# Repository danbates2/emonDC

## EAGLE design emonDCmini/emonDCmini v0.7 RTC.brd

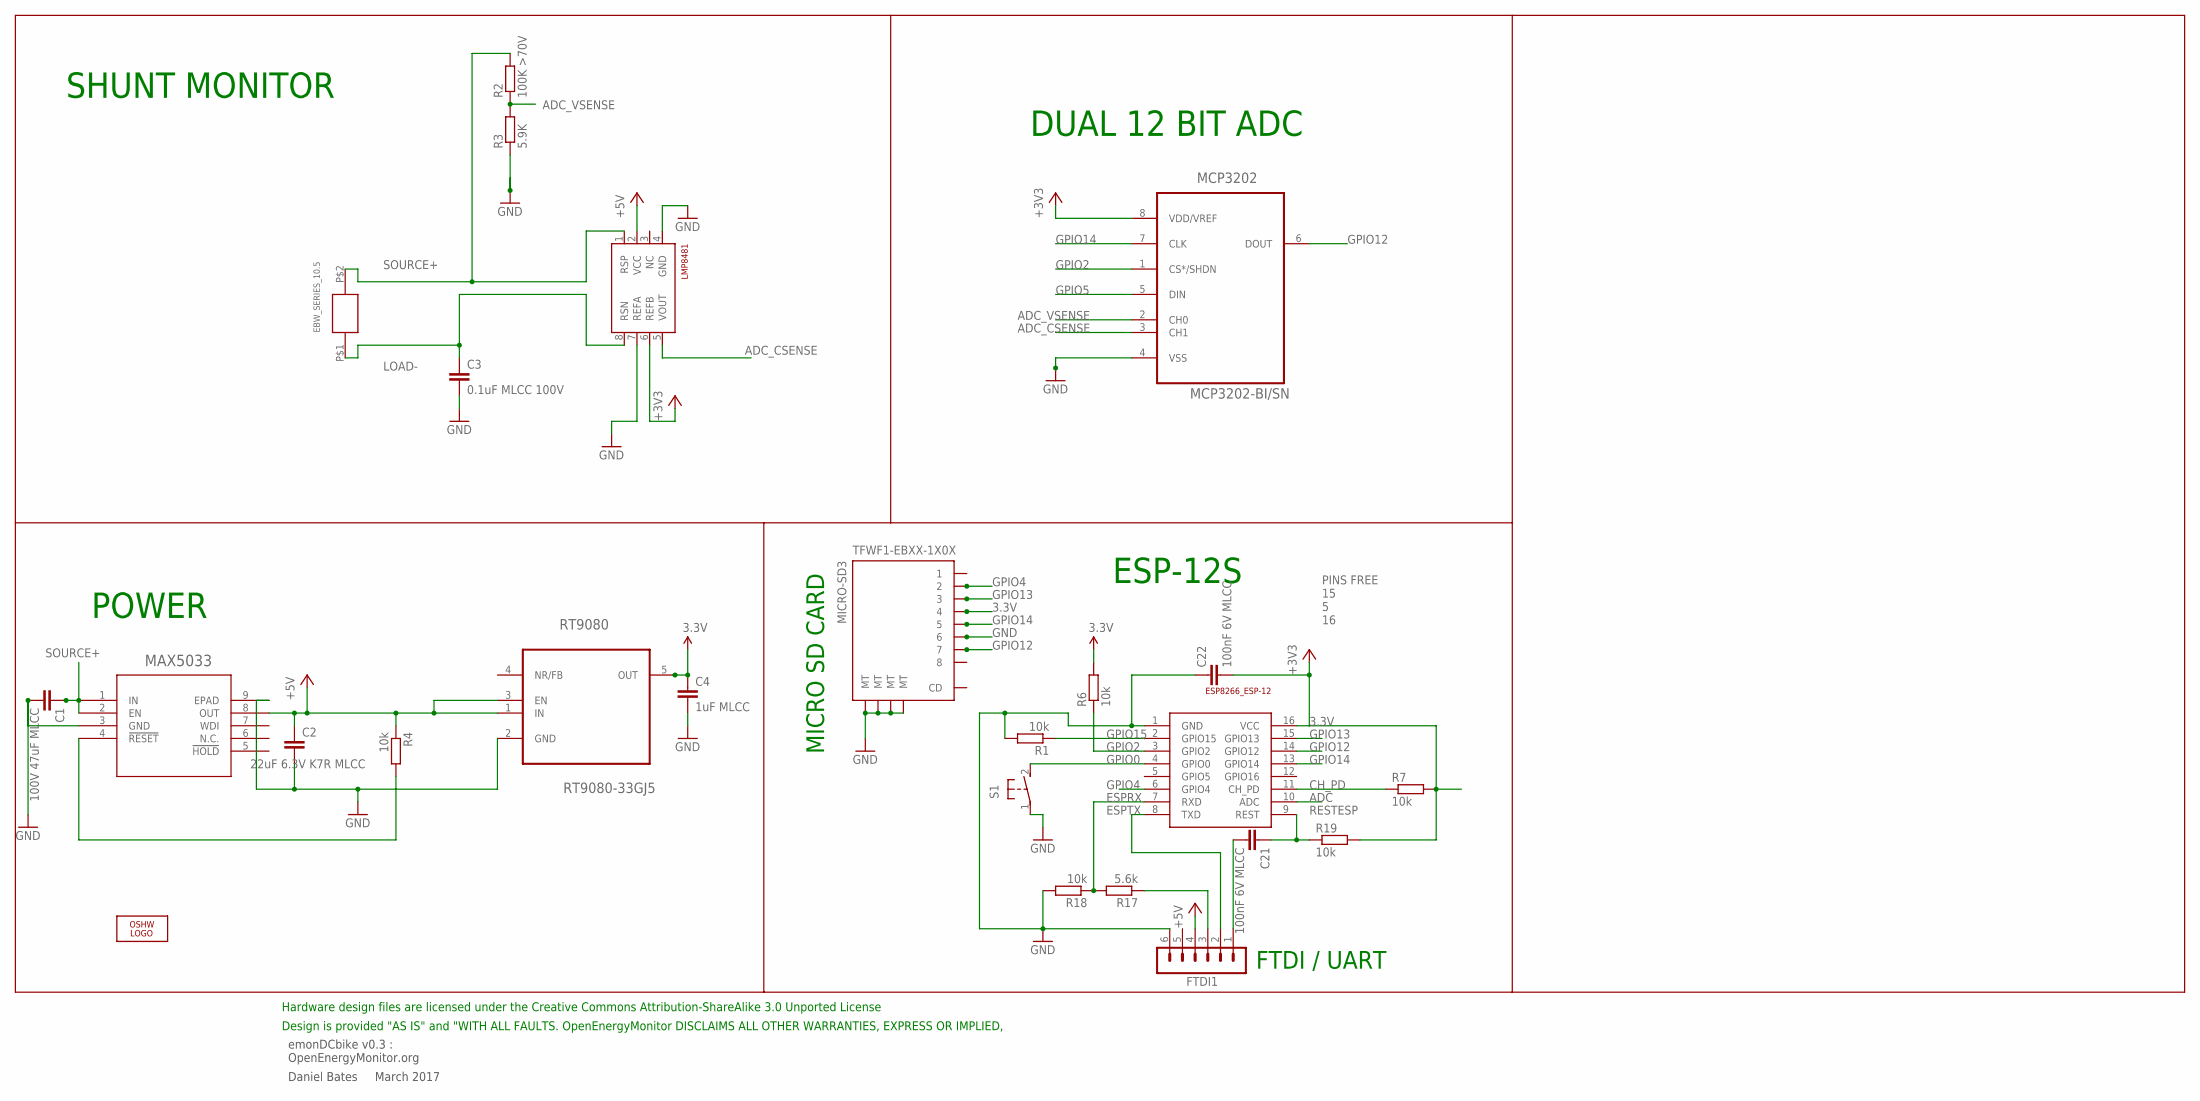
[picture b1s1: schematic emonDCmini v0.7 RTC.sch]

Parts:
C1: 100V 47uF MLCC; C1206
C2: 22uF 6.3V K7R MLCC; C1206
C3: 0.1uF MLCC 100V; C0603
C4: 1uF MLCC; C0603
C21, C22: 100nF 6V MLCC; C0603
EBW_SERIES_10.5: EBW_SERIES_10.5MM
ESP-12: ESP8266_ESP-12; ESP8266-ESP12
FTDI1: FTDI-ESP; MA06-1
LMP8481: LMP8481-H; S-PDSO-G08
LOGO1: OSHW_LOGO_6MILX0200-NT; OSHW_6X200_NOTEXT
MAX5033: MAX5033BUSA+; 21-0111D_SBE-14
MCP3202: MCP3202-BI/SN; SOIC127P600X175-8N
R1, R4, R6, R7, R18, R19: 10k; R0603
R2: 100K >70V; R0603; MPN MCWR06X1003FTL
R3: 5.9K; R0603; MPN MCWR06X5901FTL
R17: 5.6k; R0603
RT9080: RT9080-33GJ5; TSOT-23-5
S1: DTSM-3
TFWF1-EBXX-1X0X: MICRO-SD3; TF-MICRO-SD_PP3*

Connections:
3.3V: C4.1, C22.2, ESP-12.16 (VCC), LMP8481.6 (REFB), MCP3202.8 (VDD/VREF), R6.2, R7.2, R19.2, RT9080.5 (OUT), TFWF1-EBXX-1X0X.4
+5V: C2.1, FTDI1.4, MAX5033.8 (OUT), R4.1, RT9080.1 (IN), RT9080.3 (EN)
ADC: ESP-12.10 (ADC)
ADC_CSENSE: LMP8481.5 (VOUT), MCP3202.3 (CH1)
ADC_VSENSE: MCP3202.2 (CH0), R2.1, R3.2
CH_PD: ESP-12.11 (CH_PD), R7.1
ESPRX: ESP-12.7 (RXD), R17.2, R18.1
ESPTX: ESP-12.8 (TXD), FTDI1.2
GND: C1.2, C2.2, C3.2, C4.2, C22.1, ESP-12.1 (GND), FTDI1.6, LMP8481.4 (GND), LMP8481.7 (REFA), MAX5033.3 (GND), MAX5033.9 (EPAD), MCP3202.4 (VSS), R1.2, R3.1, R18.2, RT9080.2 (GND), S1.1, TFWF1-EBXX-1X0X.6, TFWF1-EBXX-1X0X.MT1 (MT), TFWF1-EBXX-1X0X.MT2 (MT), TFWF1-EBXX-1X0X.MT3 (MT), TFWF1-EBXX-1X0X.MT4 (MT)
GPIO0: ESP-12.4 (GPIO0), S1.2
GPIO2: ESP-12.3 (GPIO2), MCP3202.1 (CS*/SHDN), R6.1
GPIO4: ESP-12.6 (GPIO4), TFWF1-EBXX-1X0X.2
GPIO5: MCP3202.5 (DIN)
GPIO12: ESP-12.14 (GPIO12), MCP3202.6 (DOUT), TFWF1-EBXX-1X0X.7
GPIO13: ESP-12.15 (GPIO13), TFWF1-EBXX-1X0X.3
GPIO14: ESP-12.13 (GPIO14), MCP3202.7 (CLK), TFWF1-EBXX-1X0X.5
GPIO15: ESP-12.2 (GPIO15), R1.1
LOAD-: C3.1, EBW_SERIES_10.5.P$1, LMP8481.8 (RSN)
unnamed: MAX5033.4 (!RESET), R4.2
unnamed: FTDI1.3, R17.1
RESTESP: C21.1, ESP-12.9 (REST), R19.1
RST: C21.2, FTDI1.1
SOURCE+: C1.1, EBW_SERIES_10.5.P$2, LMP8481.1 (RSP), MAX5033.1 (IN), MAX5033.2 (EN), R2.2

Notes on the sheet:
emonDCbike v0.3 : OpenEnergyMonitor.org
Daniel Bates March 2017
Design is provided "AS IS" and "WITH ALL FAULTS. OpenEnergyMonitor DISCLAIMS ALL OTHER WARRANTIES, EXPRESS OR IMPLIED,
Hardware design files are licensed under the Creative Commons Attribution-ShareAlike 3.0 Unported License
SHUNT MONITOR
ESP-12S
MICRO SD CARD
PINS FREE 15 5 16
POWER
DUAL 12 BIT ADC
FTDI / UART
MAX5033

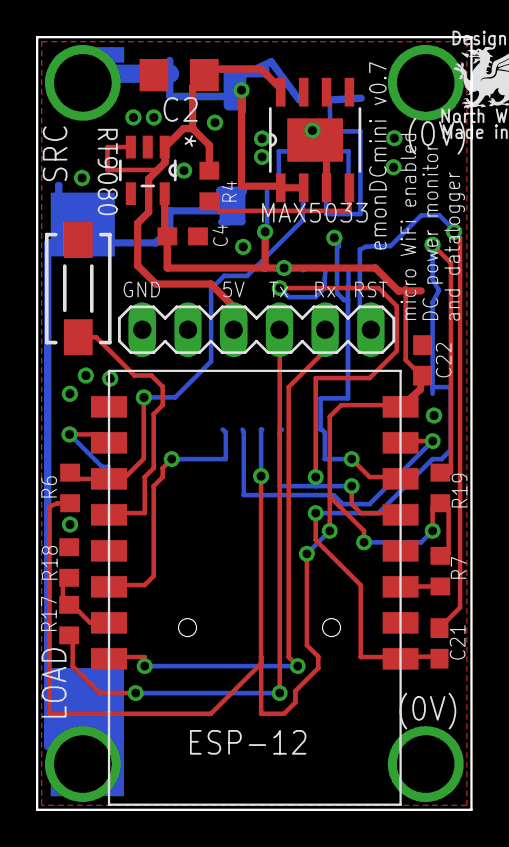
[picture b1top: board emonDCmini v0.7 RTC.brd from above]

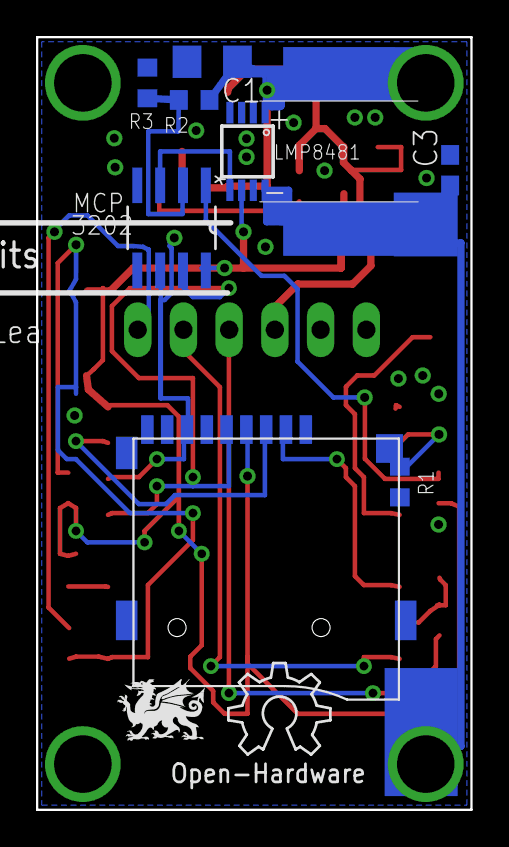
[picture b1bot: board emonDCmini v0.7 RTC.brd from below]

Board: 2 copper layers, 24.1 x 42.9 mm, 26 parts (11 on the bottom side), 21 nets.

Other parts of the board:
U$3: DRAGON_LOGO_NOTEXT

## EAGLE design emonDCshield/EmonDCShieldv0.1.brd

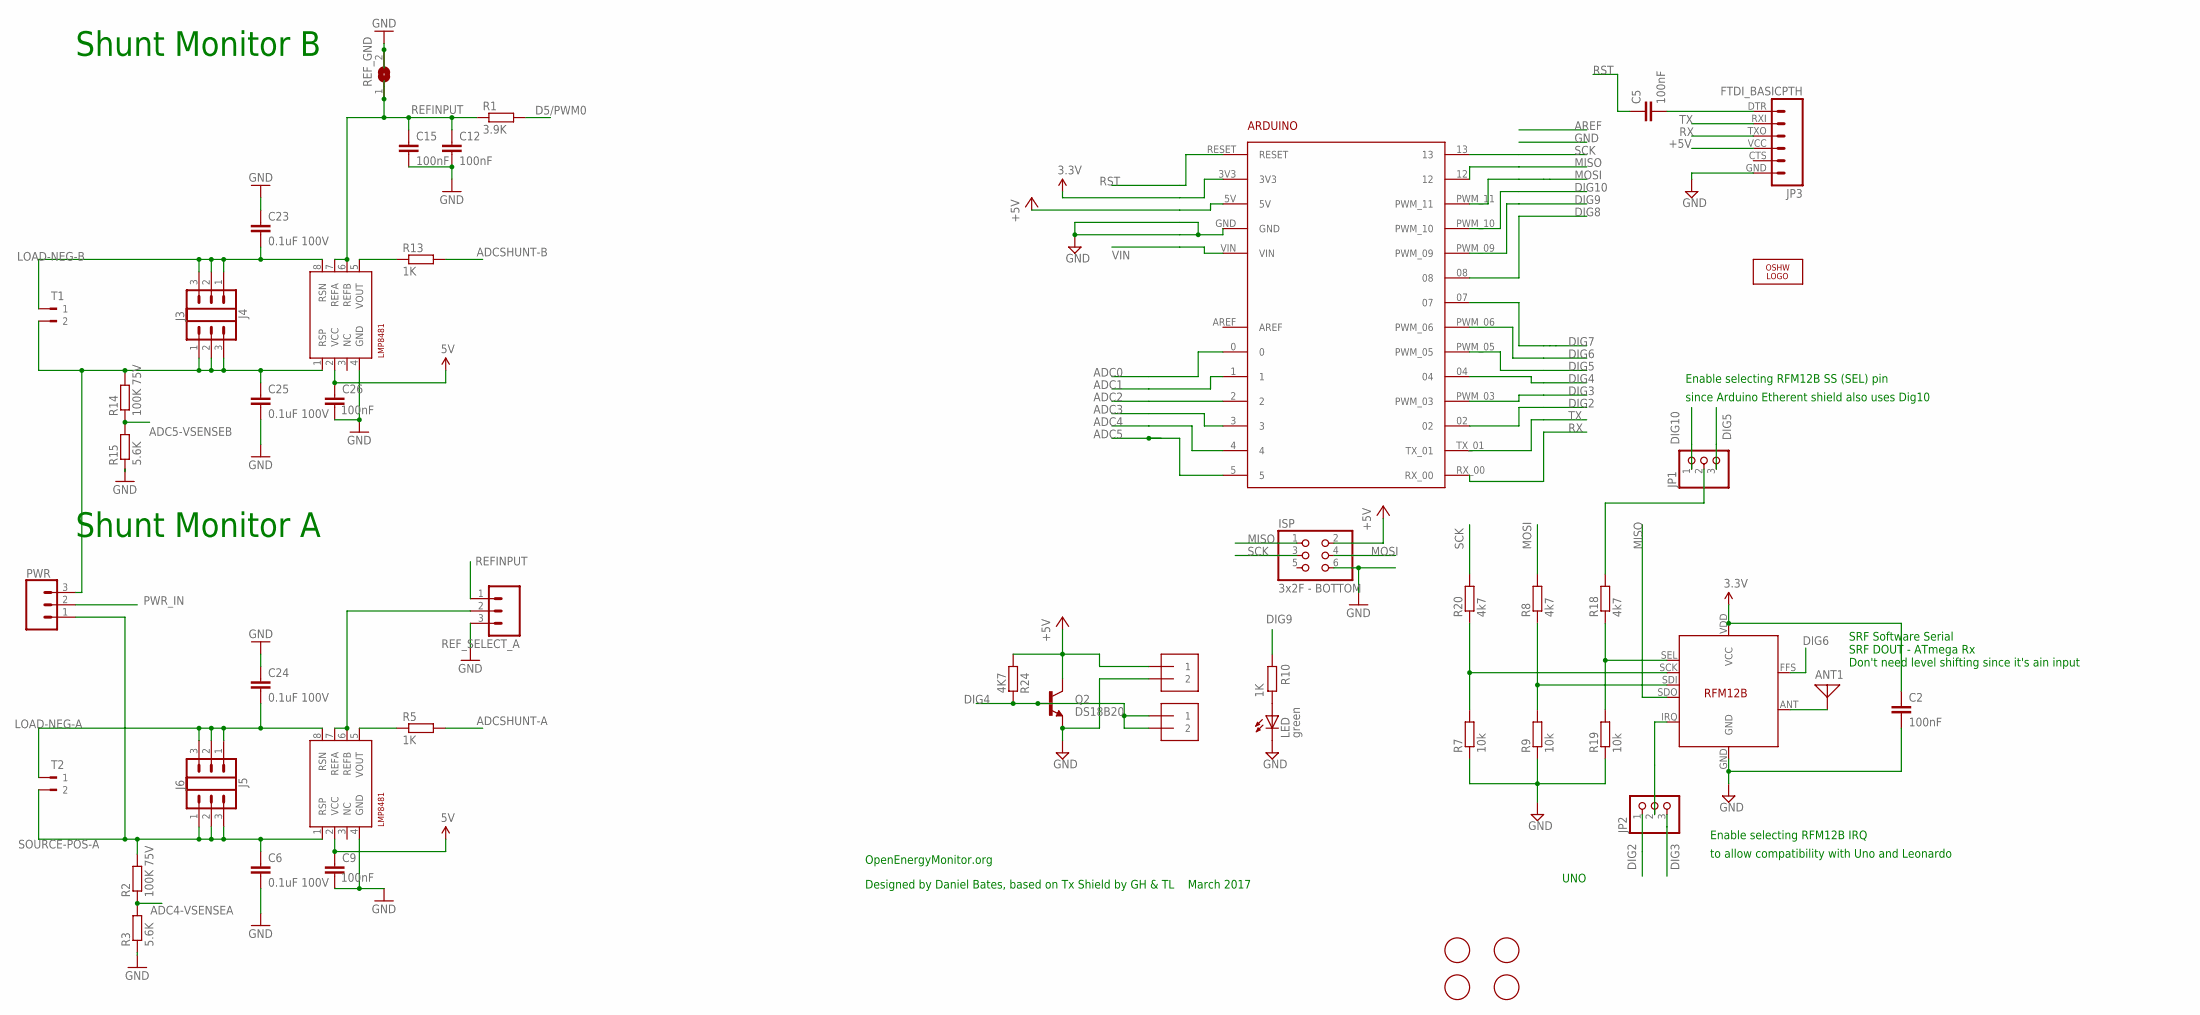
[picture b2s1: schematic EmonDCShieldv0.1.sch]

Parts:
ANT1: ANTENNA; PAD-01
ARDUINO1: ARDUINO2
C2, C5, C12: 100nF; C0603
C6, C23, C24, C25: 0.1uF 100V; C0603; MPN C1608X7S2A104K080AB
C9, C15, C26: 100nF; C0603; MPN C1608X7S2A104K080AB
ISP: 3x2F - BOTTOM; 2X03
J1, J2: 1X2-3.5MM
J3, J4, J5, J6: CONN_03; 1X03
JP1, JP2: PINHD-1X3; 1X03
JP3: FTDI_BASICPTH; FTDI_BASIC
LED: green; CHIPLED_0805
LOGO1: OSHW_LOGO_10MILX0200-NT; OSHW_10X200_NOTEXT
PWR: CONN_03; 1X03
Q2: DS18B20; TO-92
R1: 3.9K; R0603
R2, R14: 100K 75V; R0603; MPN MCWR06X1003FTL
R3, R15: 5.6K; R0603; MPN MCWR06X5901FTL
R5, R10, R13: 1K; R0603
R7, R9, R19: 10k; R0603
R8, R18, R20: 4k7; R0603
R24: 4K7; R0603
REF_GND: SJ
REF_SELECT_A: 2212S-02SG-85; 1X03; MPN 2212S-02SG-85
SHUNTMON-A: LMP8481; S-PDSO-G08; MPN LMP8481MME-S/NOPB
SHUNTMON-B: LMP8481; S-PDSO-G08; MPN LMP8481MME-H/NOPB
T1, T2: 180-2
U$1, U$3, U$4, U$5: FIDUCIAL; FIDUCIAL_1MM
U$2: RFM12B

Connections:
3.3V: ARDUINO1.3V3, C2.1, U$2.VDD (VCC)
4.7V: C9.1, C26.1, SHUNTMON-A.2 (VCC), SHUNTMON-B.2 (VCC)
+5V: ARDUINO1.5V, ISP.2, J1.1, JP3.VCC (4), Q2.3 (C), R24.1
ADC0: ARDUINO1.0
ADC1: ARDUINO1.1
ADC2: ARDUINO1.2
ADC3: ARDUINO1.3
ADC4: ARDUINO1.4
ADC4-VSENSEA: R2.1, R3.2
ADC5: ARDUINO1.5
ADC5-VSENSEB: R14.1, R15.2
ADCSHUNT-A: R5.2
ADCSHUNT-B: R13.2
D5/PWM0: R1.2
DIG2: ARDUINO1.02, JP2.1
DIG3: ARDUINO1.PWM_03, JP2.3
DIG4: ARDUINO1.04, J2.1, J2.2, Q2.2 (B), R24.2
DIG5: ARDUINO1.PWM_05, JP1.3
DIG6: ARDUINO1.PWM_06, U$2.FFS
DIG7: ARDUINO1.07
DIG8: ARDUINO1.08
DIG9: ARDUINO1.PWM_09, R10.2
DIG10: ARDUINO1.PWM_10, JP1.1
GND: ARDUINO1.GND, C2.2, C6.2, C9.2, C12.2, C15.2, C23.1, C24.1, C25.2, C26.2, ISP.6, J1.2, JP3.GND (6), LED.C, Q2.1 (E), R3.1, R7.1, R9.1, R15.1, R19.1, REF_GND.2, REF_SELECT_A.3, SHUNTMON-A.4 (GND), SHUNTMON-B.4 (GND), U$2.GND
LOAD-NEG-A: C24.2, J6.1, J6.2, J6.3, SHUNTMON-B.8 (RSN), T2.1
LOAD-NEG-B: C23.2, J3.1, J3.2, J3.3, SHUNTMON-A.8 (RSN), T1.1
MISO: ARDUINO1.12, ISP.1, U$2.SDO
MOSI: ARDUINO1.PWM_11, ISP.4, R8.2
unnamed: JP2.2, U$2.IRQ
unnamed: JP1.2, R18.2
unnamed: R5.1, SHUNTMON-B.5 (VOUT)
unnamed: R13.1, SHUNTMON-A.5 (VOUT)
unnamed: REF_SELECT_A.2, SHUNTMON-B.6 (REFB), SHUNTMON-B.7 (REFA)
unnamed: C5.2, JP3.DTR (1)
unnamed: LED.A, R10.1
unnamed: ANT1.1, U$2.ANT
unnamed: R7.2, R20.1, U$2.SCK
unnamed: R8.1, R9.2, U$2.SDI
unnamed: R18.1, R19.2, U$2.SEL
PWR_IN: PWR.2
REFINPUT: C12.1, C15.1, R1.1, REF_GND.1, REF_SELECT_A.1, SHUNTMON-A.6 (REFB), SHUNTMON-A.7 (REFA)
RST: ARDUINO1.RESET, C5.1
RX: ARDUINO1.RX_00, JP3.TXO (3)
SCK: ARDUINO1.13, ISP.3, R20.2
SOURCE-POS-A: C6.1, J5.1, J5.2, J5.3, PWR.1, R2.2, SHUNTMON-B.1 (RSP), T2.2
SOURCE-POS-B: C25.1, J4.1, J4.2, J4.3, PWR.3, R14.2, SHUNTMON-A.1 (RSP), T1.2
TX: ARDUINO1.TX_01, JP3.RXI (2)
VIN: ARDUINO1.VIN

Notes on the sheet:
Enable selecting RFM12B SS (SEL) pin
since Arduino Etherent shield also uses Dig10
Enable selecting RFM12B IRQ
to allow compatibility with Uno and Leonardo
UNO
OpenEnergyMonitor.org
Designed by Daniel Bates, based on Tx Shield by GH & TL March 2017
SRF Software Serial SRF DOUT - ATmega Rx Don't need level shifting since it's ain input
Shunt Monitor A
Shunt Monitor B

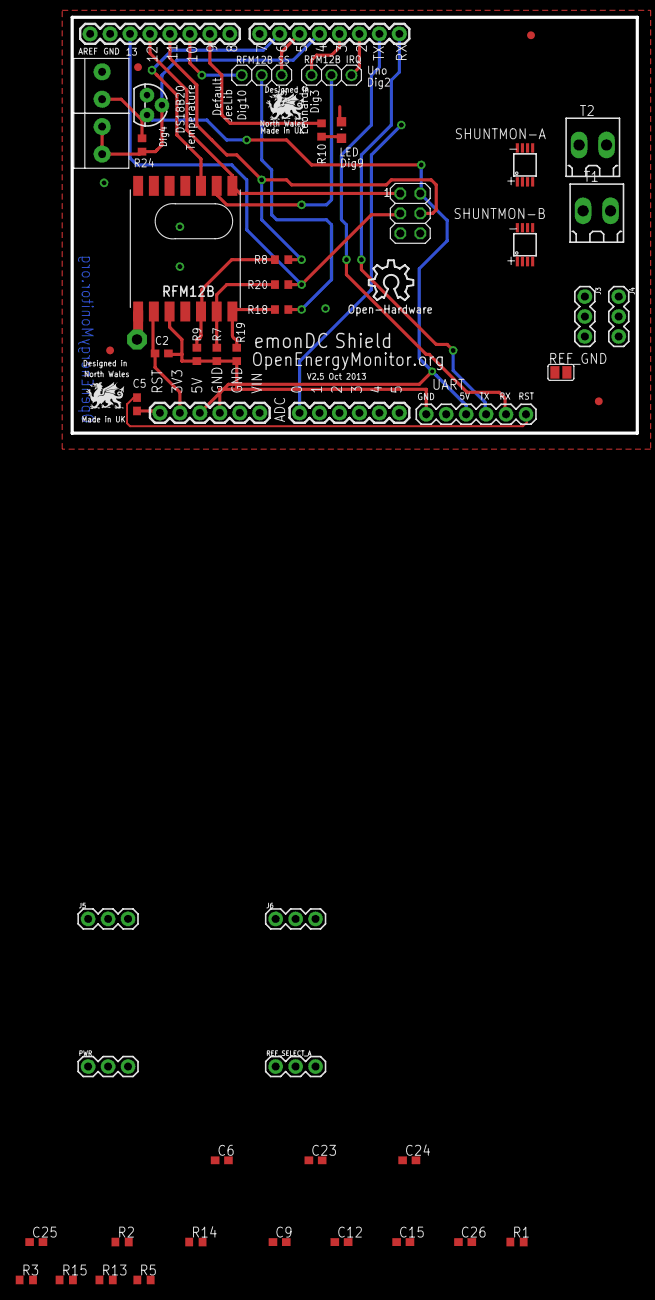
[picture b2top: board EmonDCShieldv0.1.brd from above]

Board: 2 copper layers, 72.0 x 53.0 mm, 52 parts (0 on the bottom side), 35 nets.

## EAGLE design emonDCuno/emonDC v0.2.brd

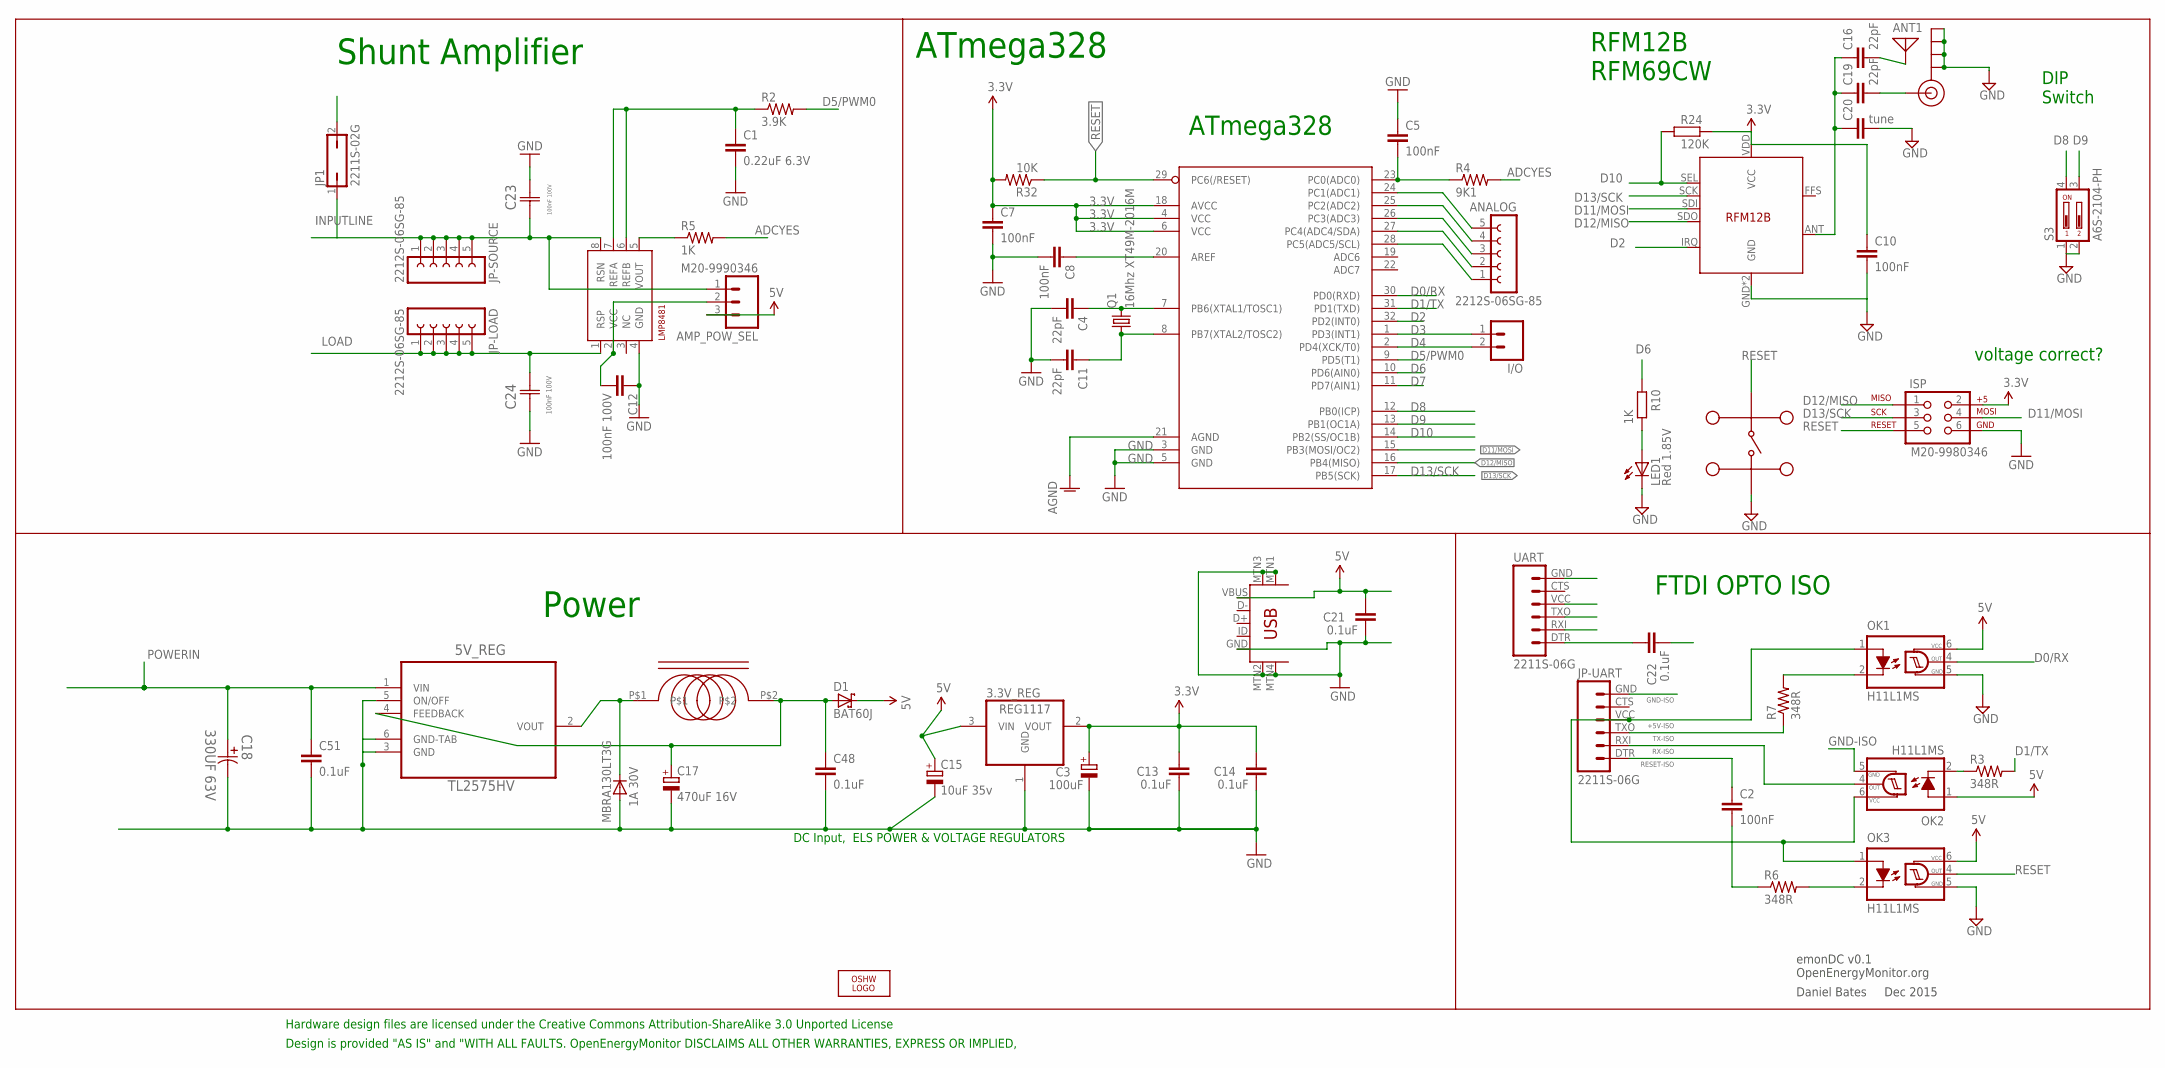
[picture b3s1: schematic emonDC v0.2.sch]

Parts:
3.3V_REG: REG1117; SOT223
5V_REG: TL2575HV; TO-263; MPN LM2575HVS-15/NOPB
AMP_POW_SEL: M20-9990346; 1X03_SMD_RA_FEMALE_NOWRITE; MPN M20-9990346
ANALOG: 2212S-06SG-85; FE05-1; MPN 2212S-06SG-85
ANT1: ANTENNA; PAD-01
C1: 0.22uF 6.3V; C0402K; MPN 04026D224KAT2A
C2, C5, C7, C8, C10: 100nF; C0402K; MPN 0402X104K100CT
C3: 100uF; 153CLV-0605; MPN UWX0J101MCL1GB
C4, C11, C16, C19: 22pF; C0603; MPN CC0402JRNPO9BN470
C12: 100nF 100V; C0805K; MPN 08051C104K4Z2A
C13, C14, C21, C22, C48: 0.1uF; C0805K; MPN 0805B104K160CT
C15: 10uF 35v; E1,8-4; MPN TAJD106K035RNJ
C17: 470uF 16V; E3,5-8; MPN 16YXF470MEFC10X12.5
C18: 330UF 63V; CAPPR500-1000X2000
C20: tune; C0603
C23, C24: 100nF 100V; CAPC1608X85N
C51: 0.1uF; C0805; MPN 0805B104K160CT
D1: BAT60J; SOD323_ST
D2: MBRA130LT3G; DO-214; MPN MBRA130LT3G
I1: SRR0603-331KL; MPN SRR0603-331KL
I/O: 2212S-02SG-85; 1X02_LOCK; MPN 2212S-02SG-85
ISP: M20-9980346; 2X3; MPN M20-9980346
J$1: SMA_EDGE; SMA-EDGE
JP1: 2211S-02G; JP1; MPN 2211S-02G
JP-LOAD: 2212S-06SG-85; FE05-1; MPN 2212S-06SG-85
JP-SOURCE: 2212S-06SG-85; FE05-1; MPN 2212S-06SG-85
JP-UART: 2211S-06G; FTDI_BASIC; MPN 2211S-06G
LED1: Red 1.85V; CHIP-LED0805; MPN SML-211UTT86K
LMP8481: LMP8481SMCLMP8481; S-PDSO-G08; MPN LMP8481MME-S/NOPB
LOGO1: OSHW_LOGO_6MILX0200-NT; OSHW_6X200_NOTEXT
OK1, OK2, OK3: H11L1MS; DIL6-SMD
Q1: 16Mhz XT49M-2016M; HC49UP; MPN XT49M-2016M
R2: 3.9K; R0603; MPN CRCW06039K09FKEA
R3, R6, R7: 348R; R0603; MPN MC0063W06031348R
R4: 9K1; R0603; MPN MC01W080559K1
R5, R10: 1K; R0603; MPN MC0063W060351K
R24: 120K; R0603; MPN RC0603FR-07120KL
R32: 10K; R0603; MPN MC0063W0603510K
RF: RFM12B
S3: A6S-2104-PH; DIP_SWITCH_SMT; MPN A6S2104H
U1_TQFP: ATMEGA328P; TQFP32-08; MPN ATMEGA328-AU
U$1: MC32882; SWITCH_TACT_MULTICOMP
UART: 2211S-06G; FTDI_BASIC; MPN 2211S-06G
USB: MUSB-05-S-B-SM-A; USB-MINIB-CISECO; MPN 67503-1020

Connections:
3.3V: 3.3V_REG.2 (VOUT), C3.+, C7.1, C10.1, C13.1, C14.1, ISP.2, R24.2, R32.2, RF.VDD (VCC), U1_TQFP.4 (VCC), U1_TQFP.6 (VCC), U1_TQFP.18 (AVCC)
5VHIGH: 5V_REG.4 (FEEDBACK), C17.+, C48.1, D1.A, I1.P$2
5VLOW: 3.3V_REG.3 (VIN), AMP_POW_SEL.3, C15.+, C21.1, D1.C, OK1.6 (VCC), OK2.1 (A), OK3.6 (VCC), UART.VCC (4), USB.VBUS
+5V-ISO: JP-UART.VCC (4), OK1.1 (A), OK2.6 (VCC), OK3.1 (A)
ADC1: ANALOG.5, U1_TQFP.24 (PC1(ADC1))
ADC2: ANALOG.4, U1_TQFP.25 (PC2(ADC2))
ADC3: ANALOG.3, U1_TQFP.26 (PC3(ADC3))
ADC4: ANALOG.2, U1_TQFP.27 (PC4(ADC4/SDA))
ADC5: ANALOG.1, U1_TQFP.28 (PC5(ADC5/SCL))
ADCYES: R4.2, R5.2
AGND: U1_TQFP.21 (AGND)
D0/RX: OK1.4 (OUT), U1_TQFP.30 (PD0(RXD)), UART.TXO (3)
D1/TX: R3.2, U1_TQFP.31 (PD1(TXD)), UART.RXI (2)
D2: RF.IRQ, U1_TQFP.32 (PD2(INT0))
D3: I/O.1, U1_TQFP.1 (PD3(INT1))
D4: I/O.2, U1_TQFP.2 (PD4(XCK/T0))
D5/PWM0: R2.2, U1_TQFP.9 (PD5(T1))
D6: R10.2, U1_TQFP.10 (PD6(AIN0))
D7: U1_TQFP.11 (PD7(AIN1))
D8: S3.4, U1_TQFP.12 (PB0(ICP))
D9: S3.3, U1_TQFP.13 (PB1(OC1A))
D9/PWM1: C1.1, LMP8481.6 (REFB), LMP8481.7 (REFA), R2.1
D10: R24.1, RF.SEL, U1_TQFP.14 (PB2(SS/OC1B))
D11/MOSI: ISP.4, RF.SDI, U1_TQFP.15 (PB3(MOSI/OC2))
D12/MISO: ISP.1, RF.SDO, U1_TQFP.16 (PB4(MISO))
D13/SCK: ISP.3, RF.SCK, U1_TQFP.17 (PB5(SCK))
DIG1: C16.1, C19.1, C20.1, RF.ANT
GND: 3.3V_REG.1 (GND), 5V_REG.3 (GND), 5V_REG.5 (ON/OFF), 5V_REG.6 (GND-TAB), C1.2, C3.-, C4.2, C5.1, C7.2, C8.2, C10.2, C11.2, C12.1, C13.2, C14.2, C15.-, C17.-, C18.2, C20.2, C21.2, C23.2 (C2), C24.1 (C1), C48.2, C51.2, D2.P$2 (A), ISP.6, J$1.GND@0 (GND), J$1.GND@1 (GND), J$1.GND@2 (GND), J$1.GND@3 (GND), LED1.C, LMP8481.4 (GND), OK1.5 (GND), OK3.5 (GND), RF.GND, RF.P$12 (GND), S3.1, S3.2, U1_TQFP.3 (GND), U1_TQFP.5 (GND), U$1.P$3, U$1.P$4, UART.GND (6), USB.GND, USB.MTN1 (MTN2), USB.MTN2 (MTN3), USB.MTN3 (MTN1), USB.MTN4
GND-ISO: JP-UART.GND (6), OK2.5 (GND)
IND: 5V_REG.2 (VOUT), D2.P$1 (C), I1.P$1
INPUTLINE: AMP_POW_SEL.1, C23.1 (C1), JP1.1, JP-SOURCE.1, JP-SOURCE.2, JP-SOURCE.3, JP-SOURCE.4, JP-SOURCE.5, LMP8481.8 (RSN)
LOAD: C24.2 (C2), JP-LOAD.1, JP-LOAD.2, JP-LOAD.3, JP-LOAD.4, JP-LOAD.5, LMP8481.1 (RSP)
unnamed: C4.1, Q1.2, U1_TQFP.7 (PB6(XTAL1/TOSC1))
unnamed: C5.2, R4.1, U1_TQFP.23 (PC0(ADC0))
unnamed: C22.1, UART.DTR (1)
unnamed: LMP8481.5 (VOUT), R5.1
unnamed: AMP_POW_SEL.2, C12.2, LMP8481.2 (VCC)
unnamed: C11.1, Q1.1, U1_TQFP.8 (PB7(XTAL2/TOSC2))
unnamed: C2.1, JP-UART.DTR (1)
unnamed: ANT1.1, C16.2
unnamed: OK1.2 (C), R7.2
unnamed: OK2.2 (C), R3.1
unnamed: OK3.2 (C), R6.2
unnamed: C8.1, U1_TQFP.20 (AREF)
unnamed: C19.2, J$1.SIG (SIGNAL)
unnamed: LED1.A, R10.1
POWERIN: 5V_REG.1 (VIN), C18.1, C51.1, JP1.2
RESET: C22.2, ISP.5, OK3.4 (OUT), R32.1, U1_TQFP.29 (PC6(/RESET)), U$1.P$1, U$1.P$2
RESET-ISO: C2.2, R6.1
RX-ISO: JP-UART.RXI (2), OK2.4 (OUT)
TX-ISO: JP-UART.TXO (3), R7.1

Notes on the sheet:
emonDC v0.1 OpenEnergyMonitor.org
Daniel Bates Dec 2015
Power
ATmega328
Design is provided "AS IS" and "WITH ALL FAULTS. OpenEnergyMonitor DISCLAIMS ALL OTHER WARRANTIES, EXPRESS OR IMPLIED,
Hardware design files are licensed under the Creative Commons Attribution-ShareAlike 3.0 Unported License
RFM12B RFM69CW
DIP Switch
FTDI OPTO ISO
DC Input, ELS POWER & VOLTAGE REGULATORS
Shunt Amplifier
voltage correct?

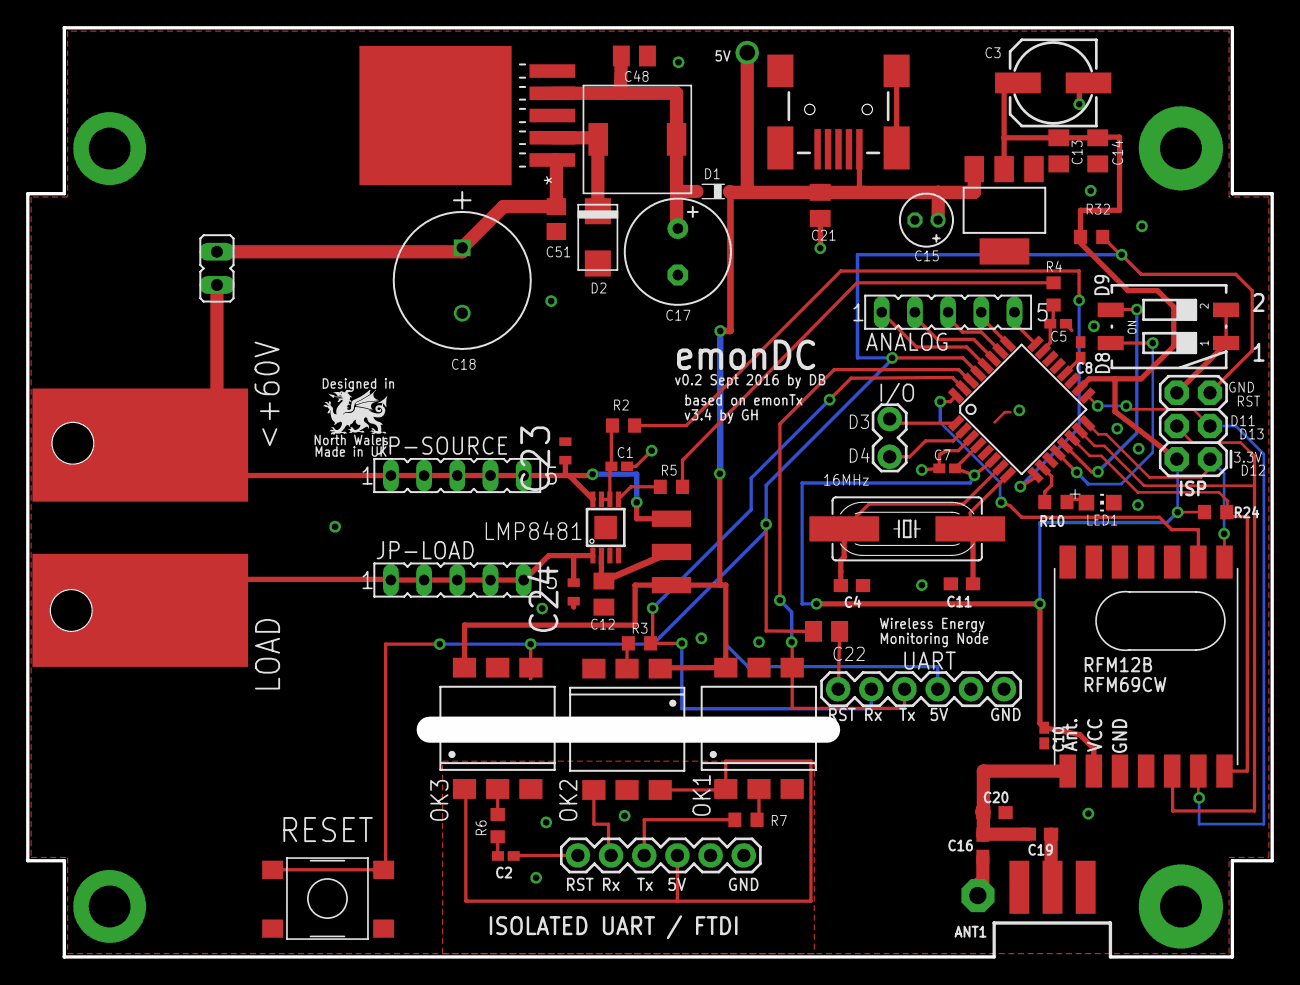
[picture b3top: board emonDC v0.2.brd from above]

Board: 2 copper layers, 95.2 x 71.1 mm, 61 parts (1 on the bottom side), 49 nets.

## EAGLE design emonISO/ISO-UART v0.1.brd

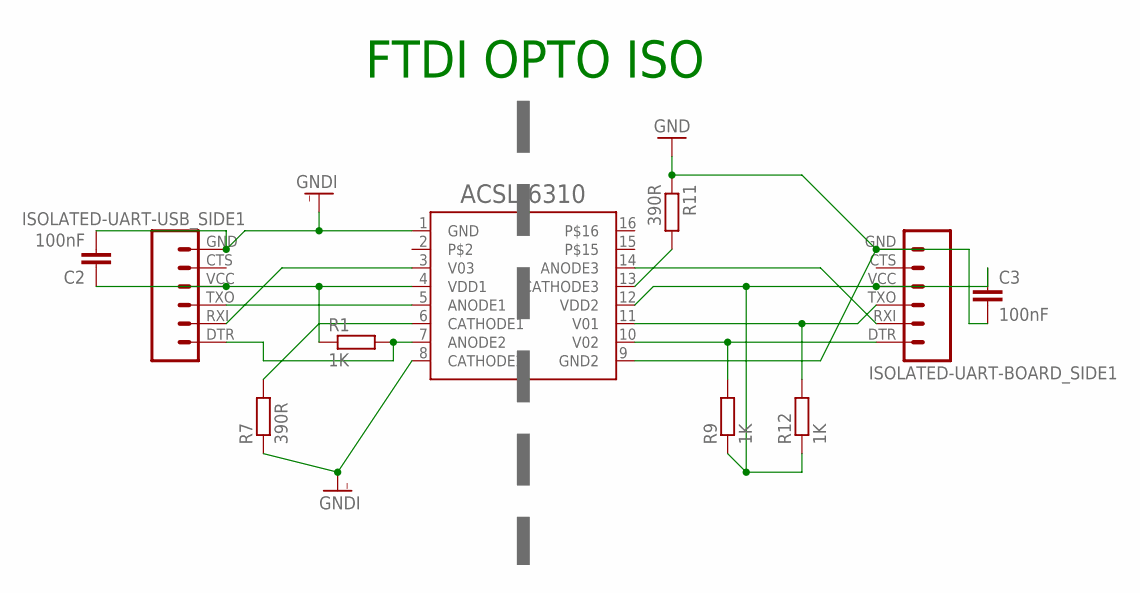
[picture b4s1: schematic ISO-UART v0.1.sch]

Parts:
ACSL-6310: ACSL-6310; SO16
C2, C3: 100nF; C0603
ISOLATED-UART-BOARD_SIDE1: 2211S-06G; FTDI_BASIC; MPN 2211S-06G
ISOLATED-UART-USB_SIDE1: 2211S-06G; FTDI_BASIC; MPN 2211S-06G
R1, R9, R12: 1K; R0603
R7, R11: 390R; R0603

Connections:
GND: ACSL-6310.9 (GND2), C3.2, ISOLATED-UART-BOARD_SIDE1.GND (6), R11.1
GNDI: ACSL-6310.1 (GND), ACSL-6310.8 (CATHODE2), C2.2, ISOLATED-UART-USB_SIDE1.GND (6), R7.1
unnamed: ACSL-6310.4 (VDD1), C2.1, ISOLATED-UART-USB_SIDE1.VCC (4), R1.1
unnamed: ACSL-6310.5 (ANODE1), ISOLATED-UART-USB_SIDE1.TXO (3)
unnamed: ACSL-6310.7 (ANODE2), ISOLATED-UART-USB_SIDE1.DTR (1), R1.2
unnamed: ACSL-6310.3 (V03), ISOLATED-UART-USB_SIDE1.RXI (2)
unnamed: ACSL-6310.10 (V02), ISOLATED-UART-BOARD_SIDE1.DTR (1), R9.2
unnamed: ACSL-6310.12 (VDD2), C3.1, ISOLATED-UART-BOARD_SIDE1.VCC (4), R9.1, R12.1
unnamed: ACSL-6310.14 (ANODE3), ISOLATED-UART-BOARD_SIDE1.RXI (2)
unnamed: ACSL-6310.6 (CATHODE1), R7.2
unnamed: ACSL-6310.13 (CATHODE3), R11.2
unnamed: ACSL-6310.11 (V01), ISOLATED-UART-BOARD_SIDE1.TXO (3), R12.2

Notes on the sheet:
FTDI OPTO ISO
ACSL-6310

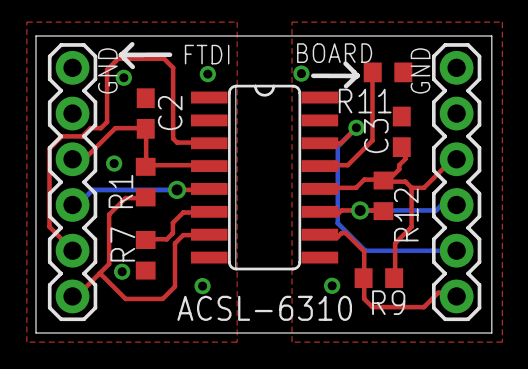
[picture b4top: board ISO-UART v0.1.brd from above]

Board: 2 copper layers, 25.3 x 16.5 mm, 10 parts (0 on the bottom side), 12 nets.

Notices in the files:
parts and their libraries:
SparkFun-Connectors: Licensing: CC v3.0 Share-Alike You are welcome to use this library for commercial purposes.
SparkFun-Aesthetics: Licensing: Creative Commons ShareAlike 4.0 International - https://creativecommons.org/licenses/by-sa/4.0
